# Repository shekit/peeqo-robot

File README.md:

# Peeqo
Thank you for making this the **~highest~ second highest voted DIY project** everr on Reddit! 
https://www.reddit.com/r/DIY/comments/5h15f4/i_built_a_desktop_robot_that_responds_entirely_in/

Check out the **video** here: https://youtu.be/ApAzIJ3jQtw

# Hardware

I have separated out the hardware elements into a seperate repo. You can find that here https://github.com/shekit/peeqo-robot-hardware

# Setting up the Pi:

This is a detailed guide on getting your Pi up and running:

### Setup up SD Card on Pi:

1. Download Raspbian Jessie with Pixel (https://www.raspberrypi.org/downloads/raspbian/)
- Kernel Version - 4.4
- Release Date - 11 - 01 - 2017 or latest version
- Version - January 2017  or latest version
2. Unzip File
- Mac OSX has problems unzipping files which unzip to more than 4gb
- Go to Terminal and unzip file with command
- tar xzvf /path/to/zip/file
3. Download Etcher from resin.io (https://etcher.io/)
4. Download SDFormatter and clean format SD card(not quick clean) -(https://www.sdcard.org/downloads/formatter_4/)
- Sometimes SD cards larger than 32GB may not work on pi
- If Pi RED LED is on, no green LED blinking, it means it cannot read the SD card
5. Transfer unzipped .img file to SD card using Etcher (etcher.io)
6. Plug SD card into Pi and boot up
7. Connect to wifi or plug in ethernet cable

### Initial Setup:

1. Go to Menu > Preferences > Raspberry Pi Config
- Set Keyboard to US
- Set Locale to your Locale
- Expand Filesystem
2. Reboot
3. Run commands in terminal to update Raspbian for recent bug fixes:
 - `sudo apt-get update` OR `sudo apt update`
 - `sudo apt-get dist-upgrade` OR `sudo apt full-upgrade`
4. Enable SSH and i2C
- `sudo raspi-config`
- Interfacing Options > SSH > Enabled
- Interfacing Options > i2c > Enabled
5. Enable overclocking or uncomment in /boot/config.txt `arm_freq=800`
6. `sudo apt install apt-transport-https`
7. Install python pillow
- `pip install pillow`
- Make sure you are using python 2.7 not 3.0+

### Update Node:

1. Raspbian ships with node v0.10.29 which will not work, have to update it
2. Remove Old Version of Node
- `sudo apt-get remove nodered -y`  (-y flag just says yes instead of requiring user input)
- `sudo apt-get remove nodejs nodejs-legacy -y`
- `sudo apt-get remove npm -y`
3. Install Latest Node Version (install version 6)
- `sudo curl -sL https://deb.nodesource.com/setup_6.x | sudo -E bash -`
- `sudo apt-get install nodejs -y`
4. Check node and npm version
- `node -v`
- Output should be v6.10.10 or higher
- `npm -v`
- Output should be 3.10.10 or higher

### Install Electron:

1. Install Electron globally (currently have v1.6.2)
- `sudo npm install -g electron`
2. If this doesn’t work
```
rm -rf ~/.electron
mkdir ~/.electron
chmod 777 ~/.electron
sudo rm /usr/bin/electron
sudo npm -g install electron
```
### Clone this repo:

```
cd ~
git clone https://github.com/shekit/peeqo-robot
```

### Start App on Boot/Startup:

1. Change into directory
 - `~/.config/autostart`
 - You may need to create this directory if it doesn't exist
2. Add and edit .desktop file with any name inside this directory
- `sudo nano peeqo.desktop`
3. Edit this file
``` 
[Desktop Entry]
	Type=Application
	Exec=./launch.sh
```
4. Create launcher script at root directory
```sudo nano launch.sh
sudo chmod +x launch.sh
```
5. Edit launch script
```
#!/bin/bash
cd /path/to/electron/app // this should be where the directory exists on your pi
sudo electron main.js
```

### Setup Mic:

1. Plug Sound Card into USB
2. Plug speaker and mic into soundcard
3. Do `arecord -l` and `aplay -l` to see the number of your device - whether it’s 0,1,2
4. Edit alsa.conf (might have to change to 1 or 2 depending on whether you have a camera plugged in)
```
sudo nano /usr/share/alsa/alsa.conf
defaults.ctl.card 0 > defaults.ctl.card 1
defaults.pcm.card 0 > defaults.pcm.card 1
defaults.pcm.device 0 > defaults.pcm.device 1
```
5. Edit aliases.conf

`sudo nano /lib/modprobe.d/aliases.conf`
- Comment out below option or it will override previous changes on startup
```
options snd-usb-audio index=-2 (comment this out with a # before)
```
- THIS MAY BE CAUSING AN ERROR, dont do this and see if it helps
- Check order modules load in
`cat /proc/asound/modules`

6. Edit .asoundrc
```
nano .asoundrc
pcm.!default{
	type asym
	playback.pcm {
		type plug
		slave.pcm “hw:1,0”  
#this first number is the number of the usb device
	}

	capture.pcm {
		type plug
		slave.pcm “hw:1,0”
 #this is the mic usb number, maybe 2 if camera is included
}
}
```
7. Check if this works instead ( this worked on one pi not running pixel)
`pcm.!default { type plug slave { pcm "hw:1,0" } } ctl.!default { type hw card 1 }`
8. If you don’t use plugs you will get following error with arecord
`arecord: set_params:1233: Sample format non available Available formats: - S16_LE`

### Setup Bluetooth:

1. `hcitool | grep ver` -- make sure it’s higher than 5.x.x
2. Stop Bluetooth Daemon bluetoothd
```
sudo systemctl stop bluetooth
sudo systemctl status bluetooth #should show status ‘quitting’
sudo systemctl disable bluetooth #for it to persist after reboot
```
3. Power up bluetooth adapter
`sudo hciconfig hci0 up`
4. Install necessary libraries
`sudo apt-get install bluetooth bluez libbluetooth-dev libudev-dev`
5. Allow to run without root/sudo
```
sudo apt-get install libcap2-bin
sudo setcap cap_net_raw+eip $(eval readlink -f `which electron`)
```
- This grants electron cap_net_raw priveleges to start/stop ble advertising
(this is not working right now)
6. Do all this before installing an app with bleno

### Remove Mouse Cursor and prevent screen from going off:

`sudo nano /etc/lightdm/lightdm.conf`
- Uncomment any line saying xserver-command=X
- Write command
`xserver-command=X -nocursor -s 0 -dpms`

### Manga Screen Settings:

```
sudo nano /boot/config.txt
hdmi_force_hotplug=1 (if not already there)
config_hdmi_boost=4
overscan_left=0
overscan_right=0
overscan_top=0
overscan_bottom=0
disable_overscan=1
display_rotate=1
	
hdmi_cvt=480 800 60 6
#hdmi_group=2
#hdmi_mode=87
#hdmi_drive=2
```

### Increase USB Current:

```
sudo nano /boot/config.txt
max_usb_current=1
```
### Run app:

```
cd /path/to/folder/electron
sudo electron main.js
```

# Steps Ahead

Yes, there's still work to be done. I will keep chipping away at it. Any contributions/feedback are welcome!

Let's make Peeqo the best community built robot ever!

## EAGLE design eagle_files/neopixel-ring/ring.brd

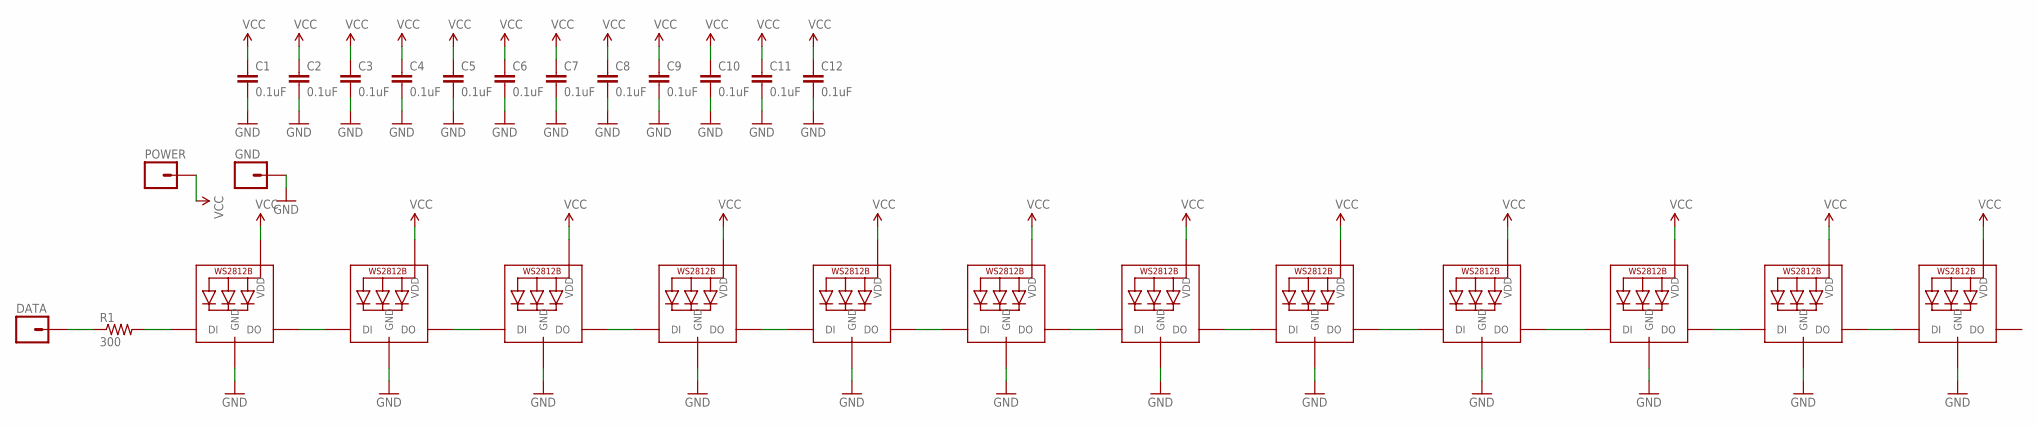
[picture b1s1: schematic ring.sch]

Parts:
C1, C2, C3, C4, C5, C6, C7, C8, C9, C10, C11, C12: 0.1uF; 0603-CAP
DATA: M01PTH; 1X01
GND: M01PTH; 1X01
LED1, LED2, LED3, LED4, LED5, LED6, LED7, LED8, LED9, LED10, LED11, LED12: WS2812B5050; WS2812B
POWER: M01PTH; 1X01
R1: 300; 0603-RES

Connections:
GND: C1.2, C2.2, C3.2, C4.2, C5.2, C6.2, C7.2, C8.2, C9.2, C10.2, C11.2, C12.2, GND.1, LED1.3-GND (GND), LED2.3-GND (GND), LED3.3-GND (GND), LED4.3-GND (GND), LED5.3-GND (GND), LED6.3-GND (GND), LED7.3-GND (GND), LED8.3-GND (GND), LED9.3-GND (GND), LED10.3-GND (GND), LED11.3-GND (GND), LED12.3-GND (GND)
unnamed: LED1.4-DIN (DI), R1.2
unnamed: DATA.1, R1.1
unnamed: LED1.2-DOUT (DO), LED2.4-DIN (DI)
unnamed: LED2.2-DOUT (DO), LED3.4-DIN (DI)
unnamed: LED3.2-DOUT (DO), LED4.4-DIN (DI)
unnamed: LED4.2-DOUT (DO), LED5.4-DIN (DI)
unnamed: LED5.2-DOUT (DO), LED6.4-DIN (DI)
unnamed: LED6.2-DOUT (DO), LED7.4-DIN (DI)
unnamed: LED7.2-DOUT (DO), LED8.4-DIN (DI)
unnamed: LED8.2-DOUT (DO), LED9.4-DIN (DI)
unnamed: LED9.2-DOUT (DO), LED10.4-DIN (DI)
unnamed: LED10.2-DOUT (DO), LED11.4-DIN (DI)
unnamed: LED11.2-DOUT (DO), LED12.4-DIN (DI)
VCC: C1.1, C2.1, C3.1, C4.1, C5.1, C6.1, C7.1, C8.1, C9.1, C10.1, C11.1, C12.1, LED1.1-VDD (VDD), LED2.1-VDD (VDD), LED3.1-VDD (VDD), LED4.1-VDD (VDD), LED5.1-VDD (VDD), LED6.1-VDD (VDD), LED7.1-VDD (VDD), LED8.1-VDD (VDD), LED9.1-VDD (VDD), LED10.1-VDD (VDD), LED11.1-VDD (VDD), LED12.1-VDD (VDD), POWER.1

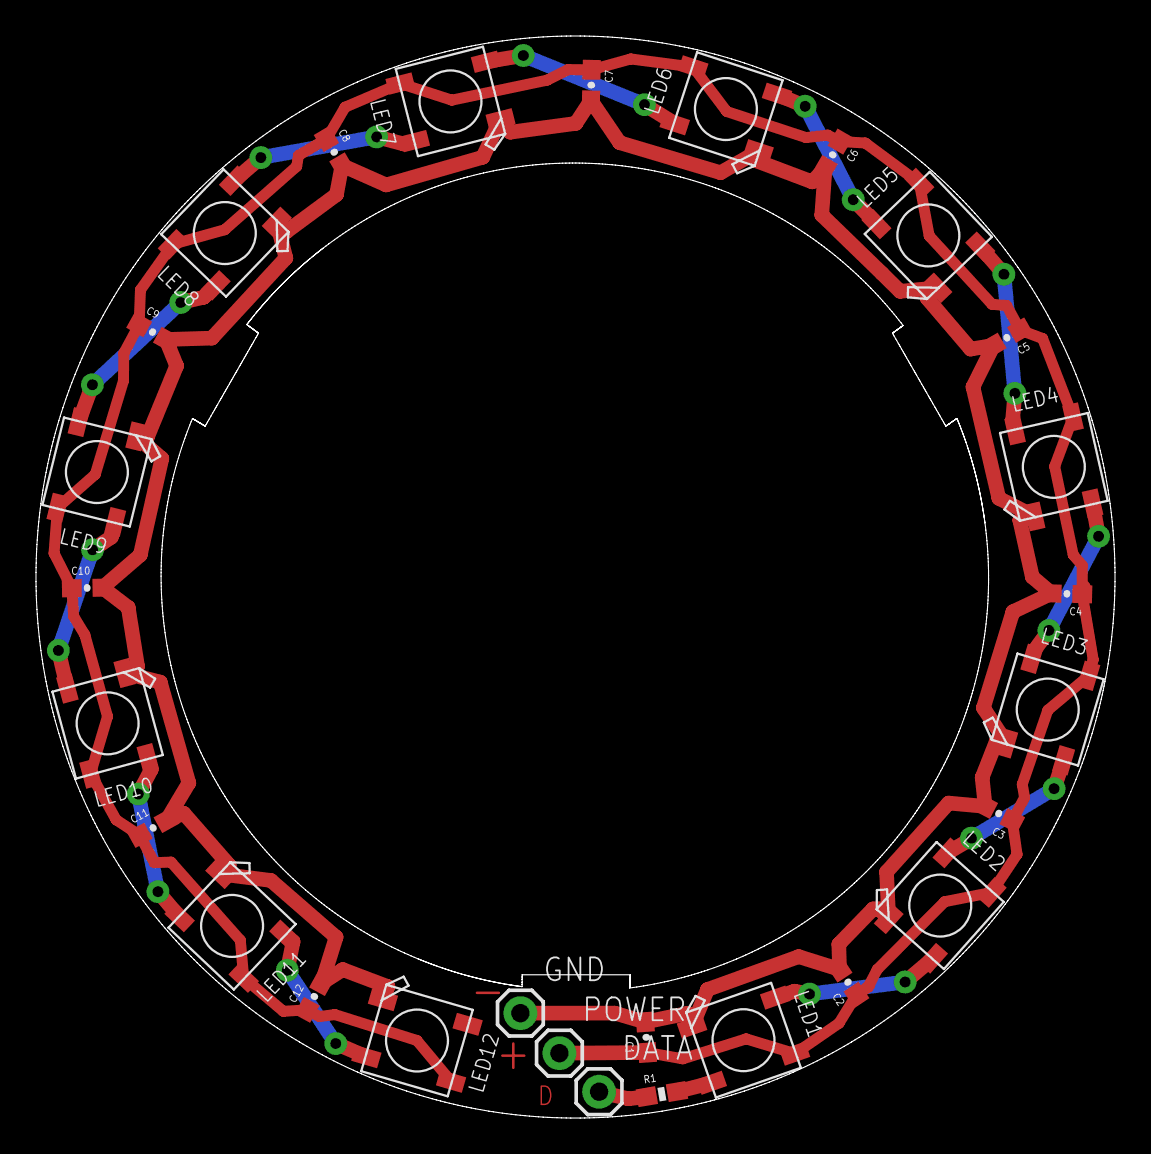
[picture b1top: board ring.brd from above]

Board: 2 copper layers, 59.9 x 60.1 mm, 28 parts (0 on the bottom side), 15 nets.

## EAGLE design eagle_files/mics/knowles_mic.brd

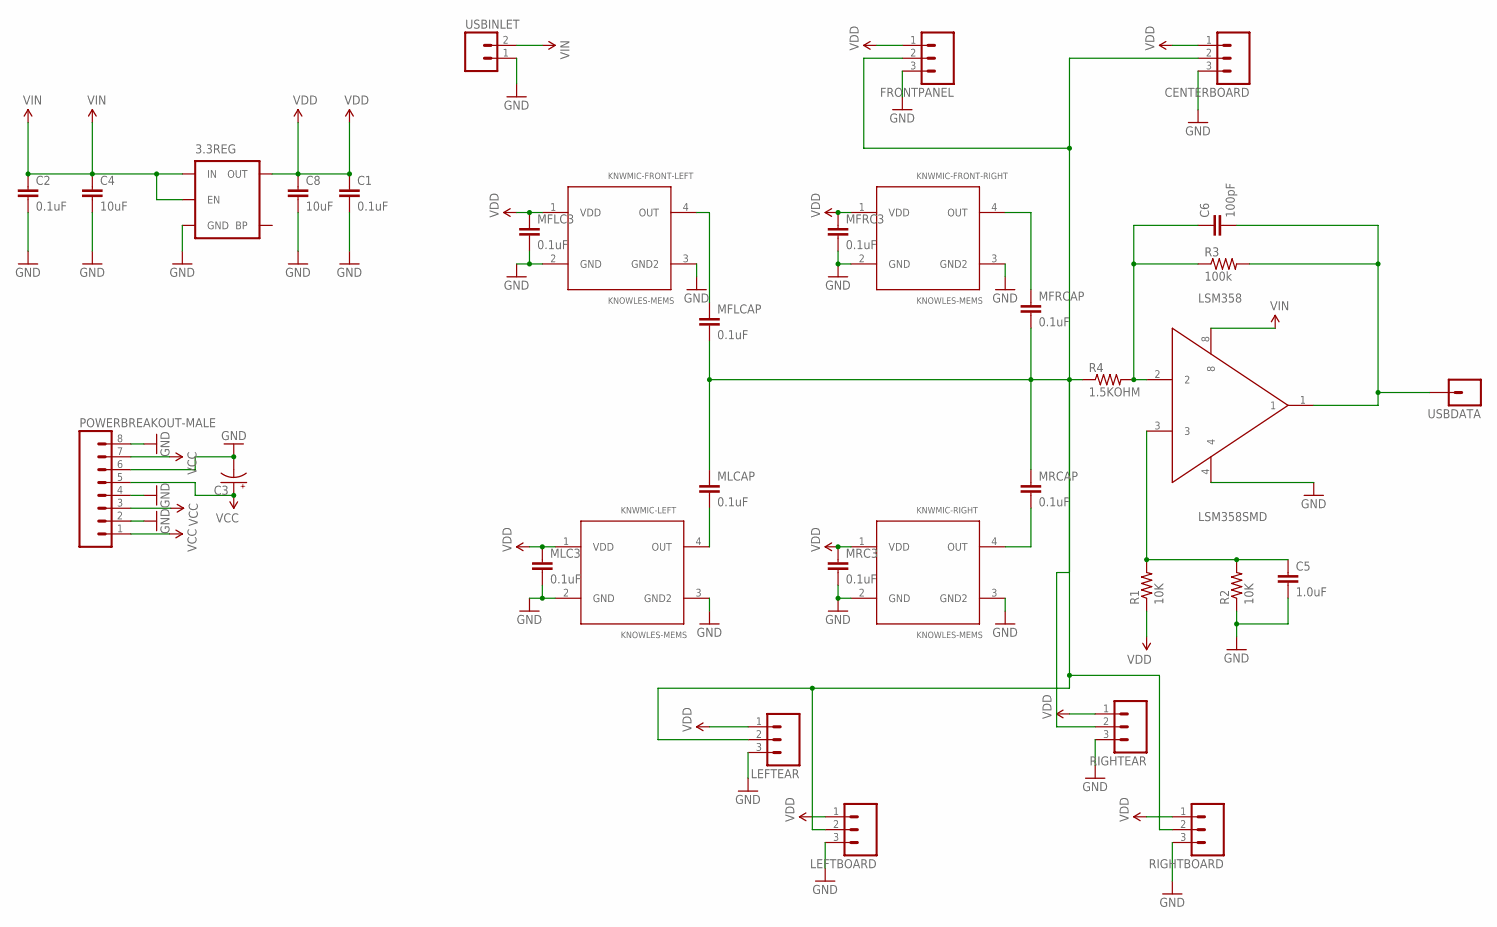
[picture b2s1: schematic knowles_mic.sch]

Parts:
3.3REG: MIC52053.3V; SOT23-5
C1, C2: 0.1uF; 0603-CAP
C3: CAP_POLG; PANASONIC_G
C4, C8: 10uF; 0603-CAP
C5: 1.0uF; 0603-CAP
C6: 100pF; 0603-CAP
CENTERBOARD: M03PTH; 1X03
FRONTPANEL: M03PTH; 1X03
KNWMIC-FRONT-LEFT: KNOWLES-MEMS; MEMS-SPU0410
KNWMIC-FRONT-RIGHT: KNOWLES-MEMS; MEMS-SPU0410
KNWMIC-LEFT: KNOWLES-MEMS; MEMS-SPU0410
KNWMIC-RIGHT: KNOWLES-MEMS; MEMS-SPU0410
LEFTBOARD: M03PTH; 1X03
LEFTEAR: M03PTH; 1X03
LSM358: LSM358SMD; SOP-8L
MFLC3: 0.1uF; 0603-CAP
MFLCAP: 0.1uF; 0603-CAP
MFRC3: 0.1uF; 0603-CAP
MFRCAP: 0.1uF; 0603-CAP
MLC3: 0.1uF; 0603-CAP
MLCAP: 0.1uF; 0603-CAP
MRC3: 0.1uF; 0603-CAP
MRCAP: 0.1uF; 0603-CAP
POWERBREAKOUT-MALE: M08SMD-STRAIGHT-FEMALE; 1X08_SMD
R1, R2: 10K; 0603-RES
R3: 100k; 0603-RES
R4: 1.5KOHM; 0603
RIGHTBOARD: M03PTH; 1X03
RIGHTEAR: M03PTH; 1X03
USBDATA: M01PTH; 1X01
USBINLET: M02PTH; 1X02

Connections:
GND: 3.3REG.2 (GND), C1.2, C2.2, C3.-, C4.2, C5.2, C8.2, CENTERBOARD.3, FRONTPANEL.3, KNWMIC-FRONT-LEFT.2 (GND), KNWMIC-FRONT-LEFT.3 (GND2), KNWMIC-FRONT-RIGHT.2 (GND), KNWMIC-FRONT-RIGHT.3 (GND2), KNWMIC-LEFT.2 (GND), KNWMIC-LEFT.3 (GND2), KNWMIC-RIGHT.2 (GND), KNWMIC-RIGHT.3 (GND2), LEFTBOARD.3, LEFTEAR.3, LSM358.4, MFLC3.2, MFRC3.2, MLC3.2, MRC3.2, POWERBREAKOUT-MALE.2, POWERBREAKOUT-MALE.4, POWERBREAKOUT-MALE.6, POWERBREAKOUT-MALE.8, R2.1, RIGHTBOARD.3, RIGHTEAR.3, USBINLET.1
unnamed: CENTERBOARD.2, FRONTPANEL.2, LEFTBOARD.2, LEFTEAR.2, MFLCAP.2, MFRCAP.2, MLCAP.1, MRCAP.1, R4.1, RIGHTBOARD.2, RIGHTEAR.2
unnamed: KNWMIC-RIGHT.4 (OUT), MRCAP.2
unnamed: KNWMIC-FRONT-LEFT.4 (OUT), MFLCAP.1
unnamed: KNWMIC-LEFT.4 (OUT), MLCAP.2
unnamed: C5.1, LSM358.3, R1.2, R2.2
unnamed: KNWMIC-FRONT-RIGHT.4 (OUT), MFRCAP.1
unnamed: C6.1, LSM358.2, R3.1, R4.2
unnamed: C6.2, LSM358.1, R3.2, USBDATA.1
VCC: C3.+, POWERBREAKOUT-MALE.1, POWERBREAKOUT-MALE.3, POWERBREAKOUT-MALE.5, POWERBREAKOUT-MALE.7
VDD: 3.3REG.5 (OUT), C1.1, C8.1, CENTERBOARD.1, FRONTPANEL.1, KNWMIC-FRONT-LEFT.1 (VDD), KNWMIC-FRONT-RIGHT.1 (VDD), KNWMIC-LEFT.1 (VDD), KNWMIC-RIGHT.1 (VDD), LEFTBOARD.1, LEFTEAR.1, MFLC3.1, MFRC3.1, MLC3.1, MRC3.1, R1.1, RIGHTBOARD.1, RIGHTEAR.1
VIN: 3.3REG.1 (IN), 3.3REG.3 (EN), C2.1, C4.1, LSM358.8, USBINLET.2

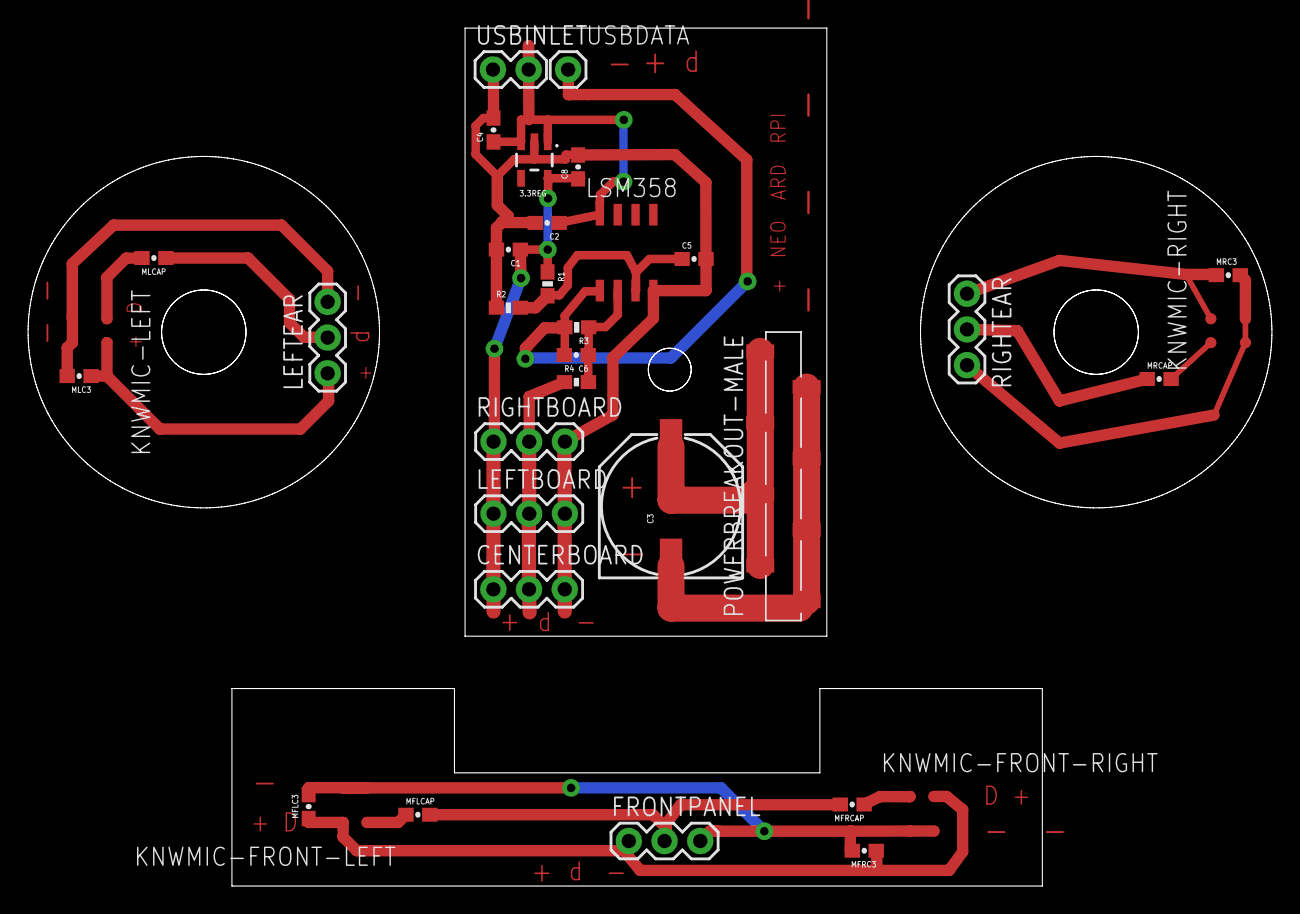
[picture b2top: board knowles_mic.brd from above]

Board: 2 copper layers, 88.5 x 61.0 mm, 34 parts (0 on the bottom side), 12 nets.

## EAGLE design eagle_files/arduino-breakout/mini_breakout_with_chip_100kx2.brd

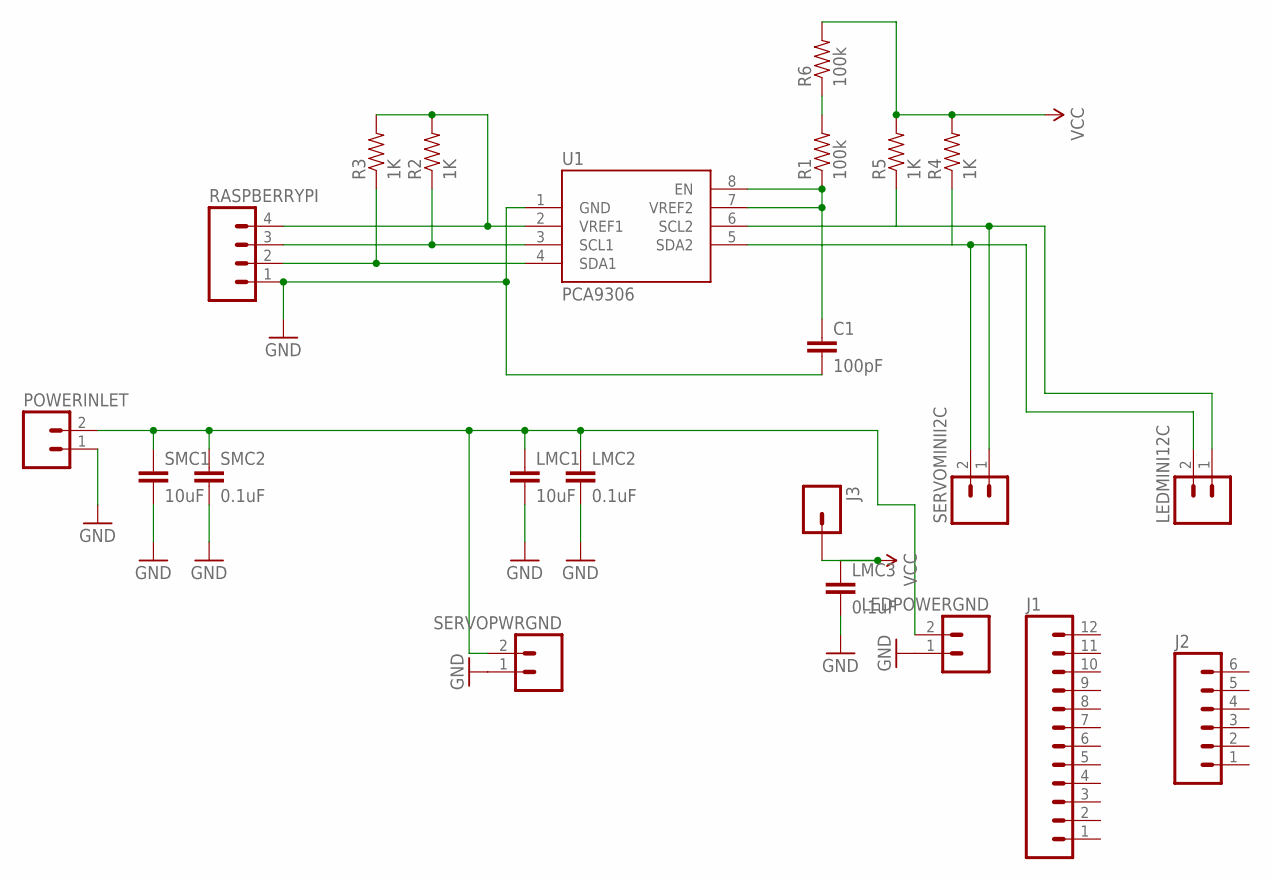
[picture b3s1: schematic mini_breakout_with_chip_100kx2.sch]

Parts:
C1: 100pF; 0603-CAP
J1: M121X12_NO_SILK_KIT; 1X12_NO_SILK_KIT
J2: M06NO_SILK_YES_STOP; 1X06_NO_SILK_YES_STOP
J3: M01NOSILK-KIT; 1X01NS-KIT
LEDMINI12C: M02PTH; 1X02
LEDPOWERGND: M021X02_NO_SILK; 1X02_NO_SILK
LMC1: 10uF; 0603-CAP
LMC2, LMC3: 0.1uF; 0603-CAP
POWERINLET: M02PTH; 1X02
R1, R6: 100k; 0603-RES
R2, R3, R4, R5: 1K; 0603-RES
RASPBERRYPI: M04PTH; 1X04
SERVOMINII2C: M02PTH; 1X02
SERVOPWRGND: M021X02_NO_SILK; 1X02_NO_SILK
SMC1: 10uF; 0603-CAP
SMC2: 0.1uF; 0603-CAP
U1: PCA9306; PSOP-8

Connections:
GND: C1.2, LEDPOWERGND.1, LMC1.2, LMC2.2, LMC3.2, POWERINLET.1, RASPBERRYPI.1, SERVOPWRGND.1, SMC1.2, SMC2.2, U1.1 (GND)
unnamed: R2.2, R3.2, RASPBERRYPI.4, U1.2 (VREF1)
unnamed: R2.1, RASPBERRYPI.3, U1.3 (SCL1)
unnamed: R3.1, RASPBERRYPI.2, U1.4 (SDA1)
unnamed: LEDPOWERGND.2, LMC1.1, LMC2.1, POWERINLET.2, SERVOPWRGND.2, SMC1.1, SMC2.1
unnamed: C1.1, R1.1, U1.7 (VREF2), U1.8 (EN)
unnamed: LEDMINI12C.1, R5.1, SERVOMINII2C.1, U1.6 (SCL2)
unnamed: LEDMINI12C.2, R4.1, SERVOMINII2C.2, U1.5 (SDA2)
unnamed: R1.2, R6.1
VCC: J3.1, LMC3.1, R4.2, R5.2, R6.2

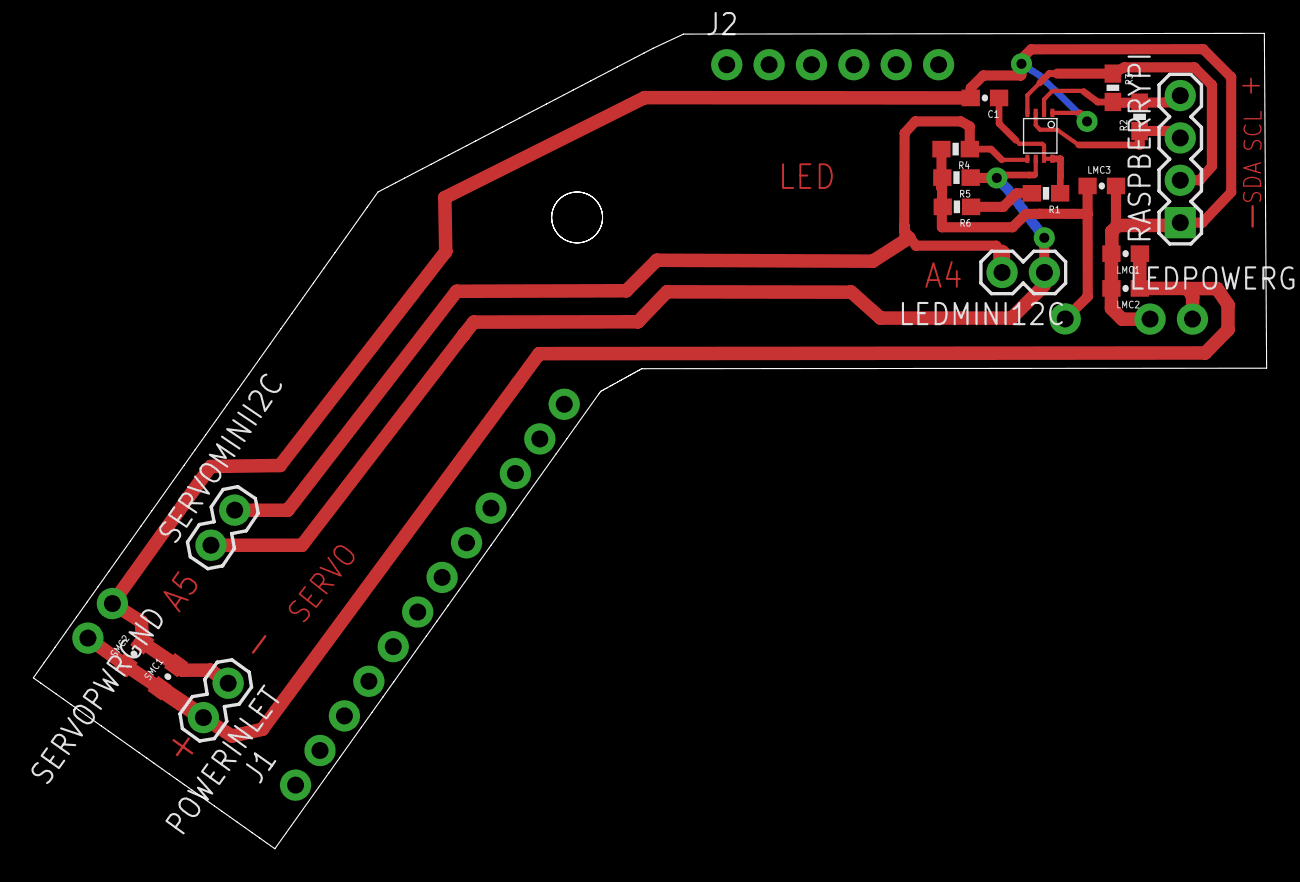
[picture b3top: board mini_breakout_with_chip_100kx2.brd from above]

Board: 2 copper layers, 73.9 x 48.9 mm, 22 parts (0 on the bottom side), 10 nets.

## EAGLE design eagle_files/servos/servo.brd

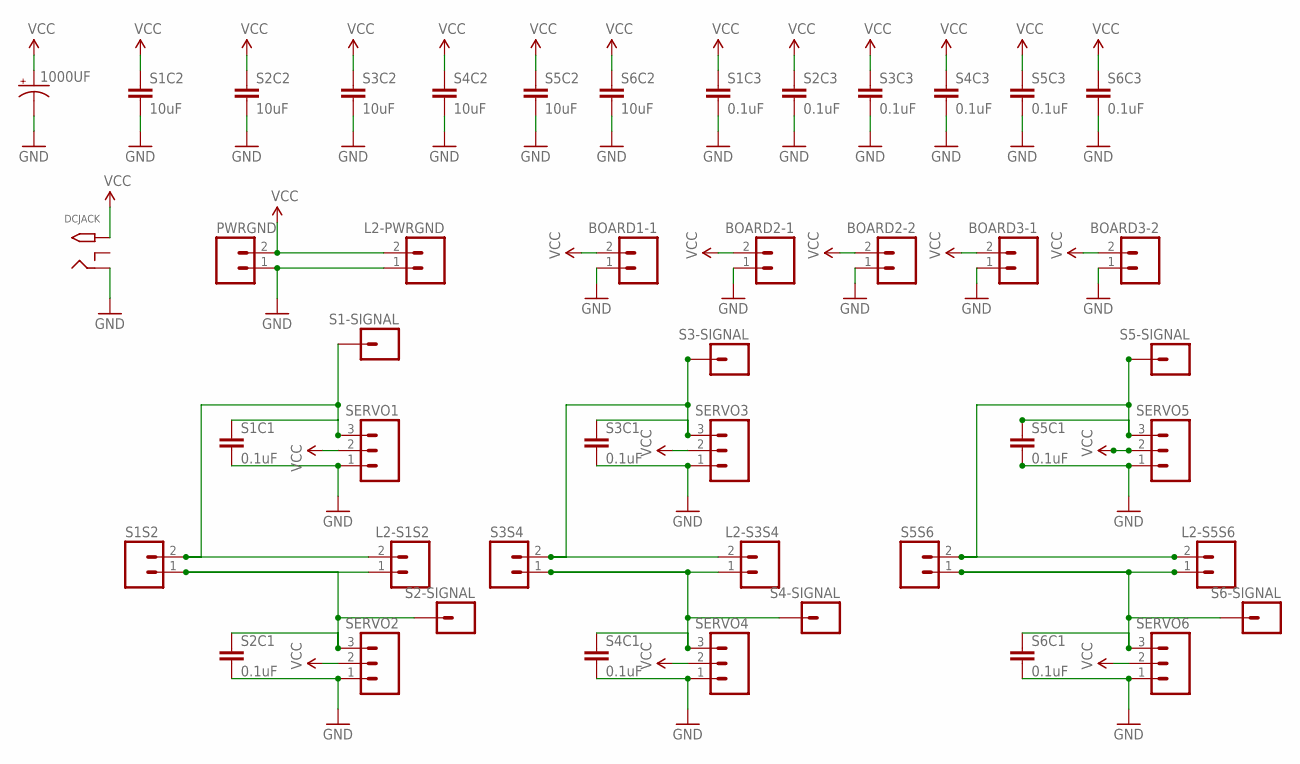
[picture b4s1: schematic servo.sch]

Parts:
1000UF: CAP_POLG; PANASONIC_G
BOARD1-1, BOARD2-1, BOARD2-2, BOARD3-1, BOARD3-2: M02PTH; 1X02
DCJACK: 2.1MMJACKTHM; PJ-102A
L2-PWRGND, L2-S1S2, L2-S3S4, L2-S5S6: M02PTH; 1X02
PWRGND: M02PTH; 1X02
S1-SIGNAL, S2-SIGNAL, S3-SIGNAL, S4-SIGNAL, S5-SIGNAL, S6-SIGNAL: M01PTH; 1X01
S1C1, S1C3, S2C1, S2C3, S3C1, S3C3, S4C1, S4C3, S5C1, S5C3, S6C1, S6C3: 0.1uF; 0603-CAP
S1C2, S2C2, S3C2, S4C2, S5C2, S6C2: 10uF; 0603-CAP
S1S2, S3S4, S5S6: M02PTH; 1X02
SERVO1, SERVO2, SERVO3, SERVO4, SERVO5, SERVO6: M03PTH; 1X03

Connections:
GND: 1000UF.-, BOARD1-1.1, BOARD2-1.1, BOARD2-2.1, BOARD3-1.1, BOARD3-2.1, DCJACK.RING, L2-PWRGND.1, PWRGND.1, S1C1.2, S1C2.2, S1C3.2, S2C1.2, S2C2.2, S2C3.2, S3C1.2, S3C2.2, S3C3.2, S4C1.2, S4C2.2, S4C3.2, S5C1.2, S5C2.2, S5C3.2, S6C1.2, S6C2.2, S6C3.2, SERVO1.1, SERVO2.1, SERVO3.1, SERVO4.1, SERVO5.1, SERVO6.1
unnamed: L2-S3S4.2, S3-SIGNAL.1, S3C1.1, S3S4.2, SERVO3.3
unnamed: L2-S1S2.2, S1-SIGNAL.1, S1C1.1, S1S2.2, SERVO1.3
unnamed: L2-S3S4.1, S3S4.1, S4-SIGNAL.1, S4C1.1, SERVO4.3
unnamed: L2-S1S2.1, S1S2.1, S2-SIGNAL.1, S2C1.1, SERVO2.3
unnamed: L2-S5S6.2, S5-SIGNAL.1, S5C1.1, S5S6.2, SERVO5.3
unnamed: L2-S5S6.1, S5S6.1, S6-SIGNAL.1, S6C1.1, SERVO6.3
VCC: 1000UF.+, BOARD1-1.2, BOARD2-1.2, BOARD2-2.2, BOARD3-1.2, BOARD3-2.2, DCJACK.TIP, L2-PWRGND.2, PWRGND.2, S1C2.1, S1C3.1, S2C2.1, S2C3.1, S3C2.1, S3C3.1, S4C2.1, S4C3.1, S5C2.1, S5C3.1, S6C2.1, S6C3.1, SERVO1.2, SERVO2.2, SERVO3.2, SERVO4.2, SERVO5.2, SERVO6.2

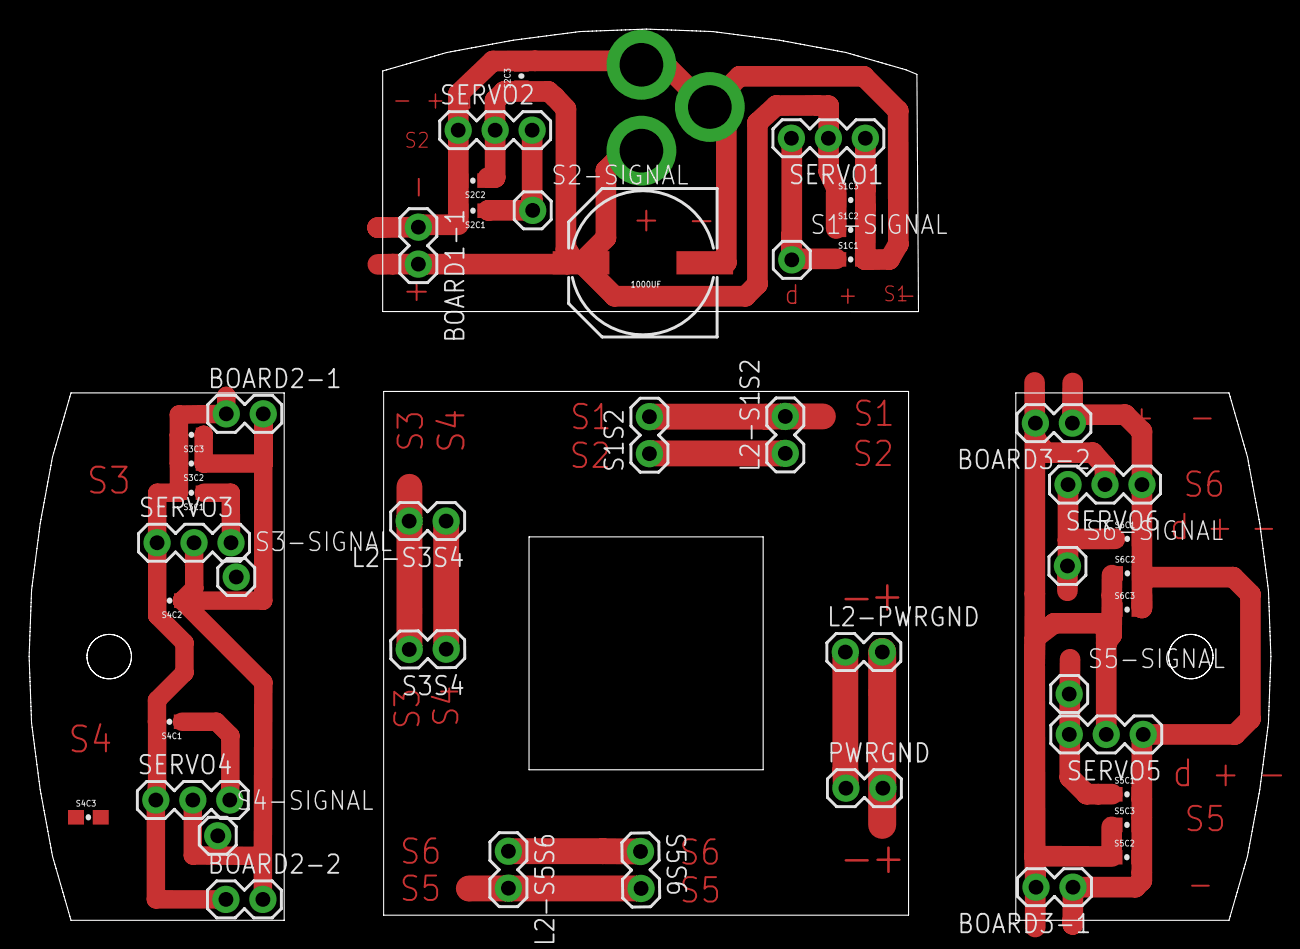
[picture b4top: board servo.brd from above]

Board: 2 copper layers, 85.3 x 61.2 mm, 45 parts (1 on the bottom side), 8 nets.

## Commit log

2016-04-11 set up basic app structure, annyang working
2016-04-11 handlebars precompilation working
2016-04-11 handlebar precompiler working
2016-04-14 basic chrome extension to detect sites for peeqo
2016-04-14 adjusted description
2016-04-15 basic server structure setup
2016-04-15 added placeholder functions
2016-04-15 edited socket event
2016-04-15 created socket link between extension, server and peeoq
2016-04-16 included spotify api
2016-04-16 added functions to deal with spotify return values
2016-04-16 included webcam test
2016-04-16 added weather api
2016-04-22 checking internet connectivity
2016-04-22 added wifi module, scanning not working
2016-04-22 added to config file
2016-04-22 removed wifi control from server
2016-04-22 implemented i2c code, not tested on pi yet
2016-04-23 added time search
2016-04-23 added moment, getting time from location
2016-04-23 wifi scanning working, still dont know reason behind bug
2016-04-23 added hammer for detecting petting swipe
2016-04-23 changed swipe to pan and included tap to annoy
2016-04-23 ble working, need to refine
2016-04-24 cordova app to connect to wifi for peeqo
2016-04-24 bluetooth changes
2016-04-24 reading ssid and pass and sending via ble
2016-04-24 fixed bug in cordova wrapper rendering
2016-04-24 tested basic communication
2016-04-24 including popup to display notes in browser
2016-04-24 working on socket links
2016-04-25 added note socket logic
2016-04-25 note display logic
2016-04-25 removed gifduration
2016-04-25 getting length of duration
2016-04-25 sending image from peeqo to extension
2016-04-25 added gif downloaded and duration finding
2016-04-25 note saving on server
2016-04-26 small changes
2016-04-26 adding socket control panel
2016-04-27 setting up structure for local gifs
2016-04-27 added eye animation
2016-04-27 adding templating
2016-04-27 code to hide and show major divs
2016-04-27 added divs
2016-04-27 added route and template for listening button
2016-04-27 tested i2c, added shutdown command
2016-04-27 added routes for remote listening and shutdown
2016-04-27 styling changes
2016-04-28 refining function callback structure
2016-04-28 added socket fall backs for remote control
2016-04-28 refining downloaded vs local functions
2016-04-28 ability to change glasses
2016-04-28 deleted unused packages
2016-04-28 split up wifi name and password page
2016-04-28 connect to wifi when ble psswd received
2016-04-28 added ability to stop ble advertising from pi
2016-04-28 added new characteristic to stop ble advertising
2016-04-28 edited top nav
2016-04-28 added more personalization functions
2016-04-28 fixed syntax bugs
2016-04-28 added python script to generate gif json
2016-04-28 added path module for path joining
2016-04-28 put check in python gif file list generator
2016-04-28 added more checks to optimize downloaded gifs
2016-04-28 added more local gifs
2016-04-29 added random blinking and image to cover div
2016-05-01 added arduino code for led and servo minis
2016-05-01 integrated i2c communication in led sketch
2016-05-01 created function to switch off all led states
2016-05-01 refining led code
2016-05-01 implementing count to repeat led animations
2016-05-01 set global animation count variable
2016-05-01 allowing for continous or limited animation
2016-05-01 added limiting to all animations
2016-05-01 comments
2016-05-01 adding servo functions
2016-05-01 using cmd para from node to set easing duration
2016-05-01 added function to reset servos to centre
2016-05-01 code to calibrate and find midpoint of each servo in microseconds
2016-05-02 processing sketch to figure out platform positions
2016-05-02 added i2c functions
2016-05-02 adding interaction logic and flor
2016-05-02 added petting and corrected some gif search errors
2016-05-03 added movement animation function
2016-05-03 added reset function, need to find angle values of servos
2016-05-03 added function to cycle through expressions
2016-05-03 arduino serial tester for processing sketch
2016-05-03 added function to send led animation
2016-05-03 added control panel and socket events
2016-05-03 rebuilt ios app with some changes, still to test
2016-05-03 added separate routes for shutdown and listen
2016-05-03 prep for push to pi, uncommented i2c lines
2016-05-03 changed socket url
2016-05-03 refined functions
2016-05-03 added reboot socket message
2016-05-03 corrected jade error
2016-05-03 open dev tools only if its on mac
2016-05-03 fixed css error
2016-05-06 added socket links for testing
2016-05-06 added test socket links
2016-05-08 added socket to find pi's ip address for sshing into it
2016-05-09 added more socket links to control panel
2016-05-09 more demo things added
2016-05-09 pic should open on extension
2016-05-10 refined demo control panel
2016-05-10 added icon
2016-05-10 tweaking demo and gifs
2016-05-10 added more demo items
2016-05-10 added more commands i2c
2016-05-10 refinin picture interaction
2016-05-10 refined cam interaction
2016-05-10 more gifs
2016-05-10 uncommented i2c
2016-05-10 added more bulbs
2016-05-10 added light control
2016-05-10 wake up function
2016-05-10 different hello
2016-05-17 fixed reset servo bug which was recursively calling itself
2016-05-17 reduced gifshot number of frames
2016-05-17 changed idle to no and stop idle to love
2016-05-17 added no and love socket
2016-05-17 added bye movement
2016-05-17 reactivated i2c
2016-05-17 added deactivation functions
2016-05-17 added more test functions
2016-05-17 fixed css
2016-05-17 tryin pan to pet
2016-11-02 changed server url
2016-11-16 added global socket url in client side js, added i2c bus to package json
2016-12-02 added 3d files, circuit files and stl files
2016-12-10 created readme file
2016-12-17 implementing sockets to test movement via web
2016-12-17 added socket events to server
2016-12-18 added form for direct url display
2016-12-18 made form labels more clear
2016-12-18 added test online form
2016-12-18 added helper tooltips
2016-12-19 more socket tests
2016-12-21 socket test end points
2016-12-21 socket test endpoints
2017-01-07 added shutdown reboot links which seem to have got deleted
2017-01-19 ble cordova app to enter wifi creds
2017-01-19 test sockets for debugging
2017-01-19 bootstrap fix
2017-01-19 margin change
2017-01-19 error in socket msg
2017-02-23 added GNU GPLv3
2017-02-23 added sample config.js file
2017-03-02 small change to stewart top stl file to increase gap for wires
2017-03-02 restructured repo, moved hardware assets to sep repo
2017-03-02 added video link to readme
2017-03-02 rewritten all code
2017-03-02 edited gif array file
2017-03-14 included updated module versions
2017-03-14 updated google cloud speech api credentials, bug fixes
2017-03-14 Move from Jade to Pug
2017-03-14 separating out socket calls and cleaning frontend
2017-03-14 restructuring js folder, reriting wifi connections
2017-03-14 separated sockets into namespaces, switched to pug
2017-03-14 typo
2017-03-14 edited file paths
2017-03-14 file restructuring and path corrections to modules
2017-03-15 removed duplicated html
2017-03-15 separated out sockets into sep modules
2017-03-16 changed module paths in global, separated out intents
2017-03-16 fixed some bugs
2017-03-16 fixed recursive error of reset event
2017-03-16 implemented video mp4 search,corrected css
2017-03-16 videos from giphy working
2017-03-16 fixed data structures
2017-03-16 fixed sound file path
2017-03-16 added responses json, cleaned functions to pass only single param through
2017-03-16 corrected some typos
2017-03-16 fixed bugs
2017-03-16 fixed bug on remote gif being deleted before being shown
2017-03-16 fixed gif length bug, wrong file path
2017-03-16 admoved response to single separate function, added local gif images
2017-03-16 refined single response function, added error handling and named params
2017-03-17 rewritten everything with new single function
2017-03-17 fixed some bugs in music requests
2017-03-17 corrected io typo
2017-03-17 corrected socket file ref typo
2017-03-17 fixed errors in animate function, working with demo sockets
2017-03-17 moved server ip to separate file
2017-03-17 fixed small bug
2017-03-17 added more gif classes
2017-03-17 fixed bugs in music stopping but eyes not showing
2017-03-17 web controls sockets working
2017-03-17 added switch btns for local and remote gifs, bug fixes
2017-03-17 added led indicators in wifi and ble
2017-03-17 bug in wifi connect, listen process not workin
2017-03-17 updated package to new module versions
2017-03-17 replaced process.env.pwd with process.cwd, was not working on pi
2017-03-17 push to test
2017-04-02 included own voice library
2017-04-02 moved listen to main file
2017-04-03 moved listed to sep module
2017-04-03 reworked to include own voice library
2017-04-03 added media recorder instead of gif capture
2017-04-03 styling changes to picture wrapper
2017-04-03 reverted to pi module versions
2017-04-03 added socket endpoints for wifi connection
2017-04-06 added weather search and text overlay option
2017-04-06 socket bug
2017-04-06 socket wifi error on server
2017-04-07 pipe to google only after animation
2017-04-07 testing wifi
2017-04-07 pi utils not in conditional
2017-10-30 updating readme with pi setup
2017-10-30 updated pi setup guide

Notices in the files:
parts and their libraries:
SparkFun-Capacitors: Licensing: Creative Commons ShareAlike 4.0 International - https://creativecommons.org/licenses/by-sa/4.0
